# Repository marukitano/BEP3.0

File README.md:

# BEP3.0

**BEP3.0** is an electronics interface for classic BMW K-series motorcycles.

It was developed to make replacing the original instrument cluster ("Brotbox")
with an aftermarket speedometer easier while keeping the original wiring loom
as intact and reversible as possible.

This repository contains the **production and manufacturing files** for the
BEP3.0.

> **License notice:** The files in this repository may be copied, modified and
> used to build a BEP3.0 for **private, non-commercial purposes**.
> **Commercial use is prohibited.**
>
> The commercial right to sell BEP3.0 units is reserved exclusively to
> **Marcus Knop**. Third-party commercial manufacturing or sales require his
> explicit written permission.

## Supported motorcycles

The BEP3.0 was designed for the classic BMW K-series, including:

- BMW K75
- BMW K100
- BMW K1
- BMW K1100

Compatibility with a particular aftermarket instrument depends on the signals
and inputs supported by that instrument.

## What is in this repository?

The repository contains the files used to produce the BEP3.0 hardware, including
PCB/manufacturing data and related production files.

The files are published so that the project can be studied, preserved, repaired
and rebuilt by private users.

## License

### Allowed

- ✅ View and study the files
- ✅ Copy the files for private, non-commercial use
- ✅ Modify the files for private, non-commercial use
- ✅ Build your own BEP3.0 for private, non-commercial use
- ✅ Have a board manufactured for your own private, non-commercial use
- ✅ Share the files non-commercially if the license and attribution remain

### Not allowed

- ❌ Sell BEP3.0 units
- ❌ Sell bare PCBs based on the BEP3.0 design
- ❌ Sell kits based on the BEP3.0 design
- ❌ Offer paid manufacturing or assembly based on these files
- ❌ Use the BEP3.0 design, or substantial parts of it, in another commercial product
- ❌ Use the files for crowdfunding, pre-orders or other commercial fundraising

**All commercial rights remain reserved by Marcus Knop.**

Only Marcus Knop may offer BEP3.0 products for commercial sale. Commercial
manufacturing by third parties is only permitted with his explicit written
permission.

See [LICENSE](LICENSE) for the complete license terms.

> Because commercial use is restricted, this project is **source-available for
> private/non-commercial use** rather than open source in the OSI/open-hardware
> sense.

## Project page

More information about the BEP3.0:

https://maru-labs.com/portfolio/bep3-0-5/

## Contributions and issues

If you discover an error in the production files or documentation, please open
an issue before manufacturing a board.

## Disclaimer

The files are provided **as-is**, without warranty.

If you manufacture hardware from these files, you are responsible for checking
the design, component choices, manufacturing data, electrical safety and
suitability for your intended use.

---

**BEP3.0 / Maru Labs**  
Copyright © Marcus Knop

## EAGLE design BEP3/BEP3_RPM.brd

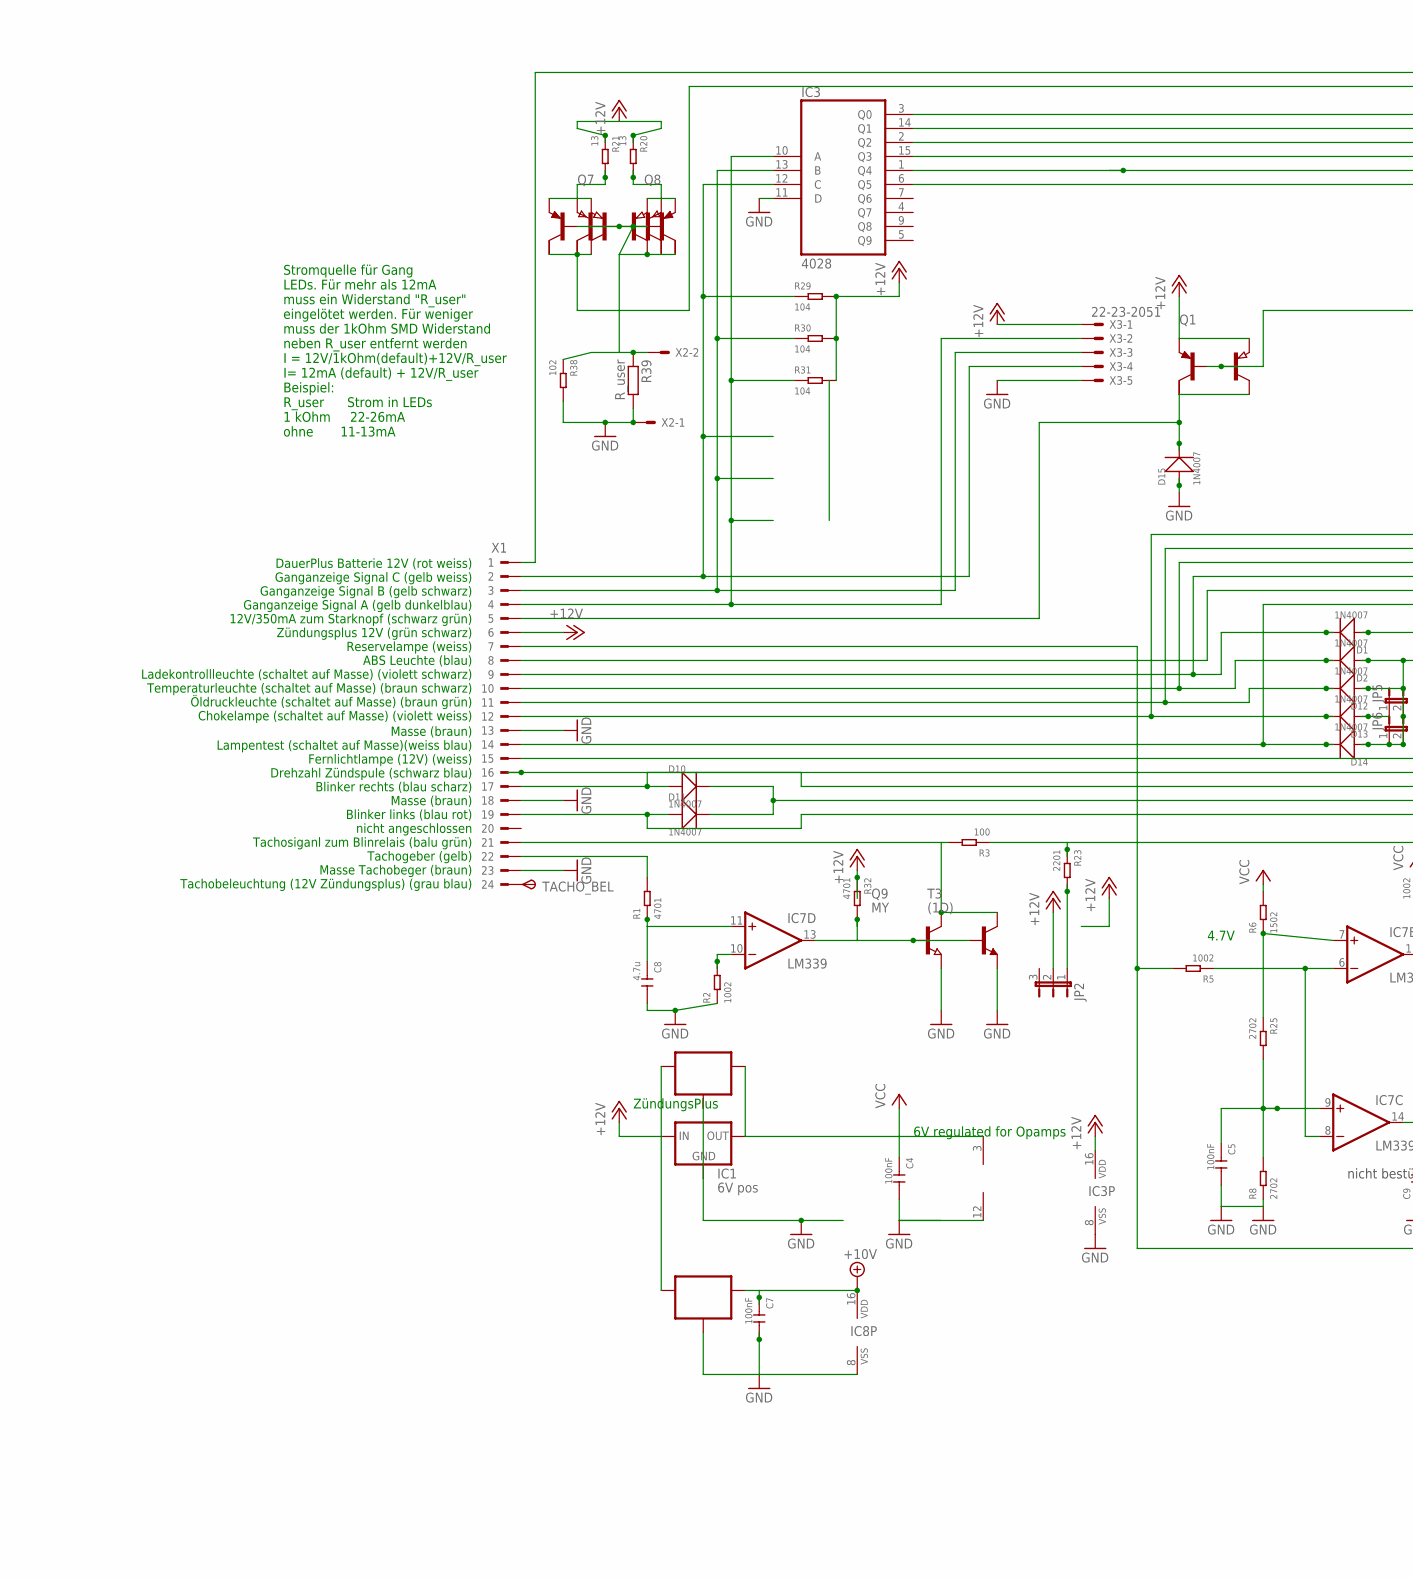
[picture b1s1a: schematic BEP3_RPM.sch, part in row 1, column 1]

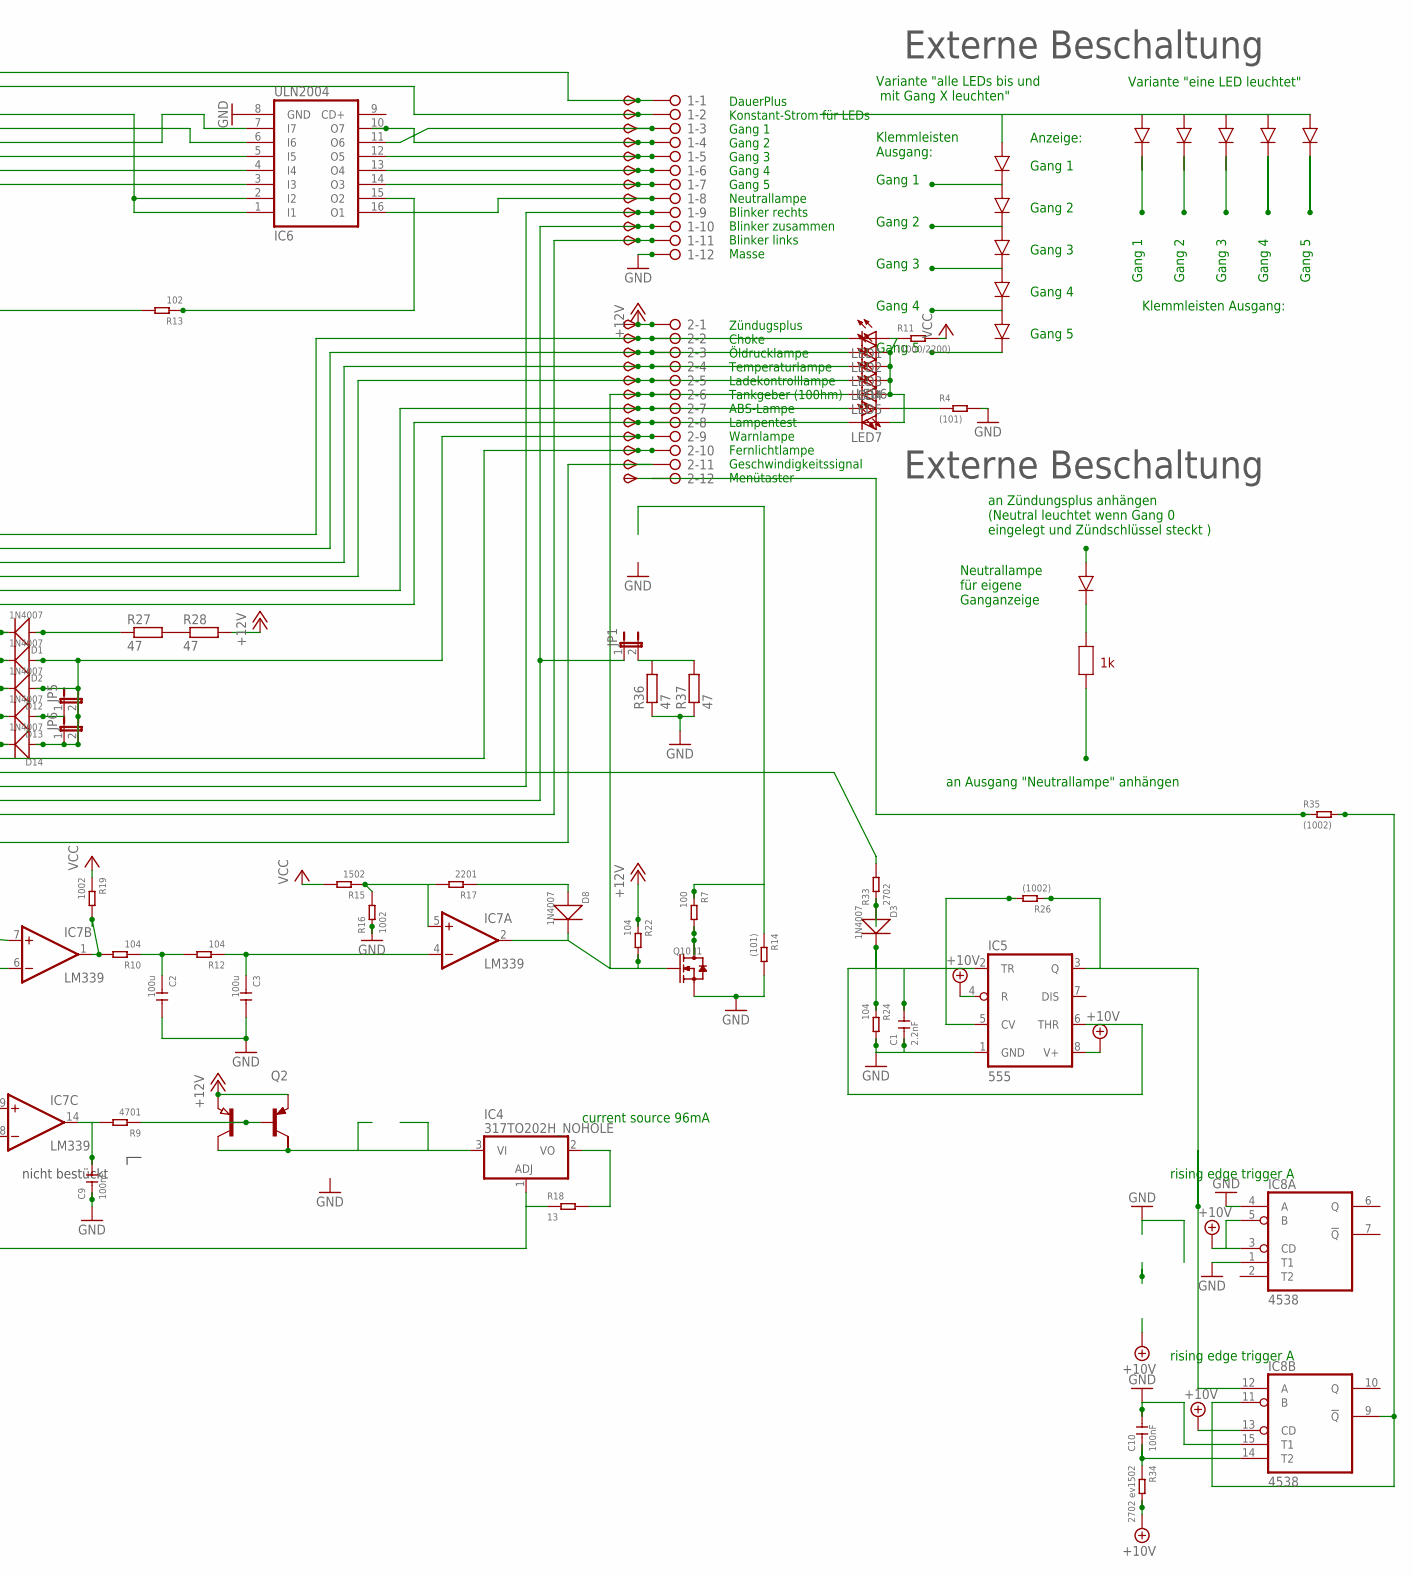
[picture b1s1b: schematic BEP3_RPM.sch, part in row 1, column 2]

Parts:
1, 2: 2081-1132; 12-PIN
C1: 2.2nF; C0805
C2, C3: 100u; C1206
C4, C5, C7, C9, C10: 100nF; C0805
C8: 4.7u; C0805
D1, D3, D10, D11, D15: 1N4007; DO-214AC
D2, D8, D12, D13, D14: 1N4007; DO-214AC-1206MOUNT
IC1: 6V pos; 78LXX
IC2, IC9: 78LXX-SOT89; SOT89
IC3: 4028; SO16
IC4: 317TO202H_NOHOLE; TO220H_NOHOLE
IC5: 555; SO08
IC6: ULN2004; SO16
IC7: LM339; SO14
IC8: 4538; SO16
JP1, JP5, JP6: JP1E; JP1
JP2: JP2E; JP2
LED1, LED2, LED3, LED4, LED5, LED6, LED7: LEDLD260; LD260
Q1, Q2, Q7, Q8: PNP-TRANSISTOR_SOT89; SOT89
Q3: AH-16; SOT223
Q4, Q5, Q6: (AH-16); SOT223
Q9: MY; SOT89
Q10: J1; SOT-23
R1, R9, R32: 4701; R0805
R2, R5, R16, R19: 1002; R0805
R3, R7: 100; R0805
R4, R14: (101); R0805
R6, R15: 1502; R0805
R8, R25, R33: 2702; R0805
R10, R12, R22, R24, R29, R30, R31: 104; R0805
R11: (1000/2200); R0805
R13, R38: 102; R0805
R17, R23: 2201; R0805
R18, R20, R21: 13; R1206
R26, R35: (1002); R0805
R27, R28, R36, R37: 47; V235/17_1MM
R34: 2702 ev1502; R0805
R39: R_user; R0805
T1: PNP2SM8; SM8
T3: (1D); SOT23-BEC
TACHO_BEL: TPSP1_1MM; P1_1.0MM
TP1, TP2, TP3, TP4, TP5, TP6, TP7, TP8, TP9, TP10, TP11, TP12, TP16, TP17, TP18, TP19, TP21, TP22, TP23, TP25, TP26: TPSB1.8; B1.8
TP13, TP24: TPSB1,27; B1,27
X1: CON_BMWV2; 24-PIN_V2
X2: 22-23-2021
X3: 22-23-2051

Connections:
+10V: C7.1, IC5.4 (R), IC5.8 (V+), IC8.3 (CD), IC8.5 (B), IC8.13 (CD), IC8.16 (VDD), IC9.1 (OUT), R34.2
+12V: 2.1, IC1.IN, IC2.3 (IN), IC3.16 (VDD), IC9.3 (IN), JP2.2, Q1.3 (E), Q2.3 (E), Q3.3 (E), Q4.3 (E), R20.1, R21.1, R22.1, R28.2, R29.2, R30.2, R31.2, R32.1, TP12.TP, X1.6, X3.1
GND: 1.12, C1.1, C2.2, C3.2, C4.2, C5.2, C7.2, C8.2, C9.1, C10.2, D15.1 (+), IC1.GND, IC2.2 (GND), IC2.4 (GND), IC3.8 (VSS), IC3.11 (D), IC5.1 (GND), IC6.8 (GND), IC7.12 (GND), IC8.1 (T1), IC8.4 (A), IC8.8 (VSS), IC8.15 (T1), Q9.3 (E), Q10.2 (S), R2.1, R4.2, R8.1, R14.2, R16.1, R24.2, R36.1, R37.1, R38.2, R39.2, T3.E, X1.13, X1.18, X1.23, X2.1, X3.5
unnamed: 2.9, D2.1 (+), D12.1 (+), D14.1 (+), JP5.2, JP6.1, JP6.2, TP24.TP
unnamed: IC3.10 (A), R31.1, X1.4, X3.2
unnamed: IC3.13 (B), R30.1, X1.3, X3.3
unnamed: 2.7, LED6.A, TP22.TP, X1.8
unnamed: Q5.3 (E), Q8.3 (E), R21.2, T1.1 (E)
unnamed: IC7.10 (-IN), R2.2
unnamed: R27.2, R28.1
unnamed: Q6.3 (E), Q7.3 (E), R20.2, T1.3 (E)
unnamed: D15.2 (-), Q1.2 (C), Q3.2 (C), X1.5
unnamed: 2.2, D13.2 (-), LED1.K (C), TP16.TP, X1.12
unnamed: 2.3, D12.2 (-), LED2.K (C), TP17.TP, X1.11
unnamed: 2.4, D2.2 (-), LED3.K (C), TP18.TP, X1.10
unnamed: IC4.3 (VI), Q2.2 (C), Q4.2 (C)
unnamed: IC7.6 (-IN), IC7.8 (-IN), R5.1
unnamed: IC3.12 (C), R29.1, X1.2, X3.4
unnamed: IC3.15 (Q3), IC6.5 (I5)
unnamed: 2.8, D14.2 (-), LED7.K (C), TP23.TP, X1.14
unnamed: 1.9, D10.1 (+), TP9.TP, X1.17
unnamed: 1.11, D11.1 (+), TP11.TP, X1.19
unnamed: IC8.9 (!Q), IC8.11 (B), R35.2
unnamed: R1.2, X1.22
unnamed: C8.1, IC7.11 (+IN), R1.1
unnamed: 1.6, IC6.13 (O4), TP6.TP
unnamed: 1.7, IC6.14 (O3), TP7.TP
unnamed: 2.11, R3.1, R23.1, TP26.TP
unnamed: R7.1, R14.1
unnamed: JP2.1, R23.2
unnamed: C5.1, IC7.9 (+IN), R8.2, R25.2
unnamed: C9.2, IC7.14 (OUT), R9.2
unnamed: C1.2, D3.2 (-), IC5.2 (TR), IC5.6 (THR), R24.1
unnamed: LED6.K (C), R4.1
unnamed: IC4.1 (ADJ), R5.2, R18.1, X1.7
unnamed: Q2.1 (B), Q4.1 (B), R9.1
unnamed: IC3.2 (Q2), IC6.7 (I7)
unnamed: 1.3, IC6.11 (O6), TP3.TP
unnamed: 1.5, IC6.12 (O5), TP5.TP
unnamed: LED1.A, LED2.A, LED3.A, LED4.A, LED5.A, LED7.A, R11.1
unnamed: R33.2, X1.16
unnamed: Q1.1 (B), Q3.1 (B), R13.2
unnamed: IC3.3 (Q0), IC6.1 (I1), IC6.2 (I2)
unnamed: C2.1, R10.1, R12.2
unnamed: C3.1, IC7.4 (-IN), R12.1
unnamed: IC7.5 (+IN), R15.1, R16.2, R17.2
unnamed: Q10.3 (D), R7.2
unnamed: D8.1 (+), R17.1
unnamed: IC3.1 (Q4), IC6.4 (I4)
unnamed: 1.8, IC6.16 (O1), TP8.TP
unnamed: 2.10, TP25.TP, X1.15
unnamed: D1.1 (+), R27.1
unnamed: 2.5, D1.2 (-), LED4.K (C), TP19.TP, X1.9
unnamed: IC3.14 (Q1), IC6.6 (I6)
unnamed: Q5.1 (B), Q6.1 (B), Q6.2 (C), Q7.1 (B), Q7.2 (C), Q8.1 (B), R38.1, R39.1, T1.2 (B), T1.4 (B), T1.6 (C1), X2.2
unnamed: TACHO_BEL.TP, X1.24
unnamed: 1.2, Q5.2 (C), Q8.2 (C), T1.8 (C1), TP2.TP
unnamed: 2.6, D8.2 (-), IC7.2 (OUT), LED5.K (C), Q10.1 (G), R22.2, TP21.TP
unnamed: IC3.6 (Q5), IC6.3 (I3)
unnamed: IC4.2 (VO), R18.2
unnamed: IC5.5 (CV), R26.2
unnamed: 1.4, IC6.10 (O7), TP4.TP
unnamed: 1.1, TP1.TP, X1.1
unnamed: IC7.7 (+IN), R6.1, R25.1
unnamed: Q9.2 (C), R3.2, T3.C, X1.21
unnamed: IC7.13 (OUT), Q9.1 (B), R32.2, T3.B
unnamed: IC5.3 (Q), IC8.12 (A), R26.1
unnamed: D3.1 (+), R33.1
unnamed: IC6.15 (O2), R13.1
unnamed: C10.1, IC8.14 (T2), R34.1
unnamed: 2.12, R35.1, TP13.TP
unnamed: 1.10, D10.2 (-), D11.2 (-), JP1.1, TP10.TP
unnamed: JP1.2, R36.2, R37.2
unnamed: D13.1 (+), JP5.1
unnamed: IC7.1 (OUT), R10.2, R19.2
VCC: C4.1, IC1.OUT, IC2.1 (OUT), IC7.3 (V+), R6.2, R11.2, R15.2, R19.1

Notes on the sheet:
6V regulated for Opamps
current source 96mA
ZündungsPlus
Zündugsplus Choke Öldrucklampe Temperaturlampe Ladekontrolllampe Tankgeber (100hm) ABS-Lampe Lampentest Warnlampe Fernlichtlampe Geschwindigkeitssignal Menütaster
DauerPlus Konstant-Strom für LEDs Gang 1 Gang 2 Gang 3 Gang 4 Gang 5 Neutrallampe Blinker rechts Blinker zusammen Blinker links Masse
DauerPlus Batterie 12V (rot weiss) Ganganzeige Signal C (gelb weiss) Ganganzeige Signal B (gelb schwarz) Ganganzeige Signal A (gelb dunkelblau) 12V/350mA zum Starknopf (schwarz grün) Zündungsplus 12V (grün schwarz) Reservelampe (weiss) ABS Leuchte (blau) Ladekontrollleuchte (schaltet auf Masse) (vi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
Masse (braun) Lampentest (schaltet auf Masse)(weiss blau) Fernlichtlampe (12V) (weiss) Drehzahl Zündspule (schwarz blau) Blinker rechts (blau scharz) Masse (braun) Blinker links (blau rot) nicht angeschlossen Tachosiganl zum Blinrelais (balu grün) Tachogeber (gelb) Masse Tachobeger (braun) Tachobel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
4.7V
Stromquelle für Gang LEDs. Für mehr als 12mA muss ein Widerstand "R_user" eingelötet werden. Für weniger muss der 1kOhm SMD Widerstand neben R_user entfernt werden I = 12V/1kOhm(default)+12V/R_user I= 12mA (default) + 12V/R_user Beispiel: R_user Strom in LEDs 1 kOhm 22-26mA ohne 11-13mA
Gang 1
Gang 2
Gang 3
Gang 4
Gang 5
Variante "eine LED leuchtet"
Variante "alle LEDs bis und mit Gang X leuchten"
Klemmleisten Ausgang:
Klemmleisten Ausgang:
an Zündungsplus anhängen (Neutral leuchtet wenn Gang 0 eingelegt und Zündschlüssel steckt )
an Ausgang "Neutrallampe" anhängen
Neutrallampe für eigene Ganganzeige
Externe Beschaltung
Anzeige:
nicht bestückt
rising edge trigger A

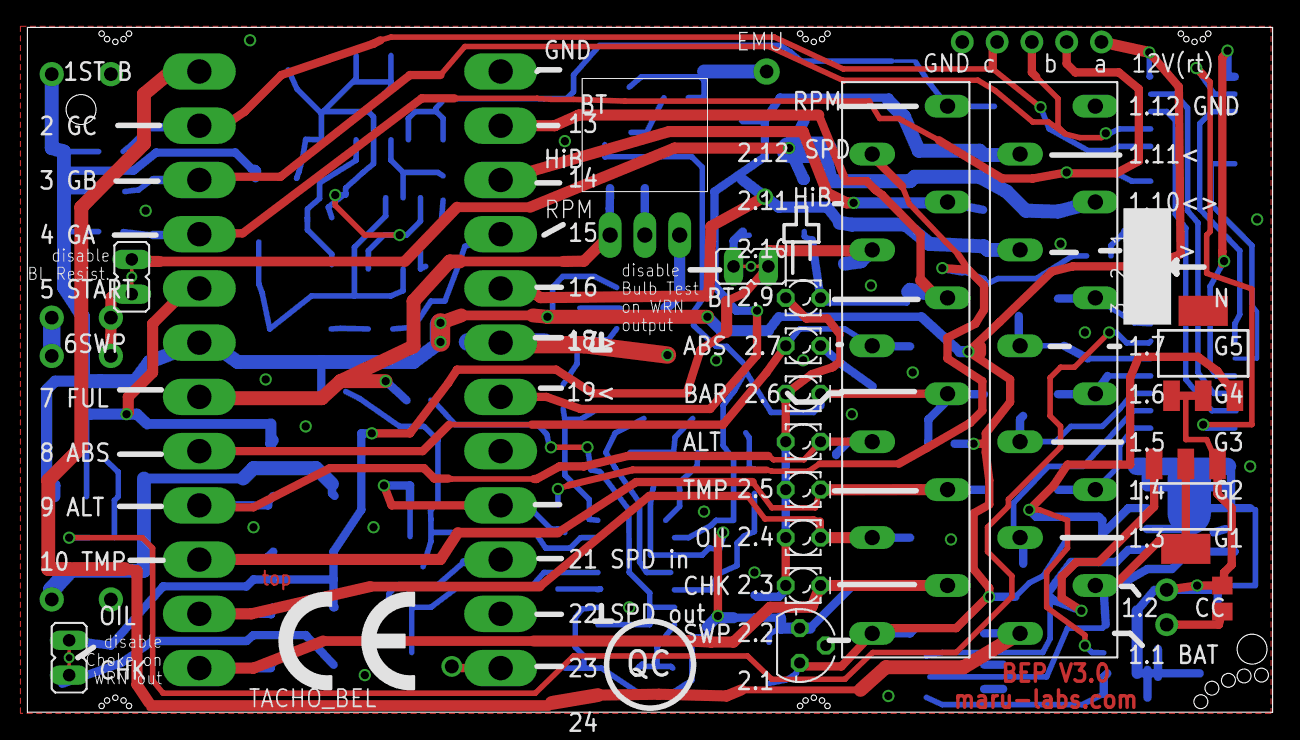
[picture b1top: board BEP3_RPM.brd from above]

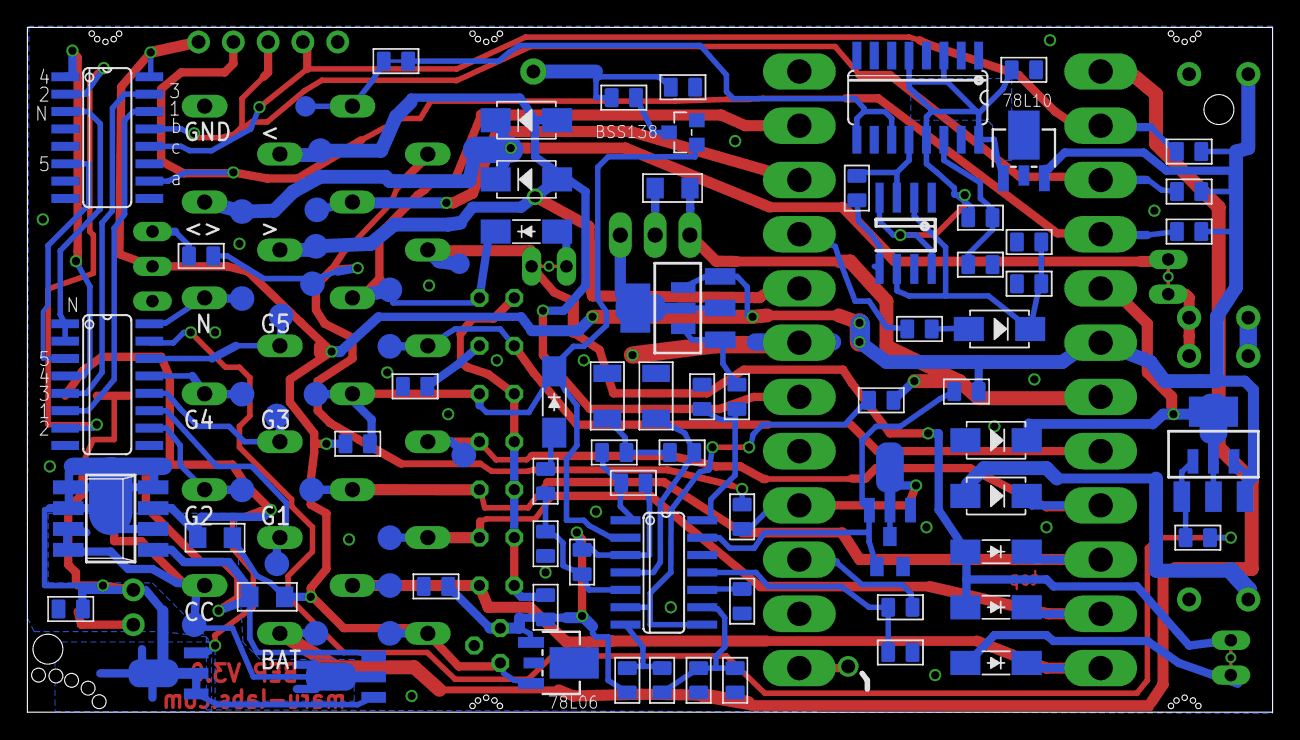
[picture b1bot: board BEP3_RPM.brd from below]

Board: 2 copper layers, 90.9 x 50.0 mm, 120 parts (94 on the bottom side), 76 nets.

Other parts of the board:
U$1: CE_10.00

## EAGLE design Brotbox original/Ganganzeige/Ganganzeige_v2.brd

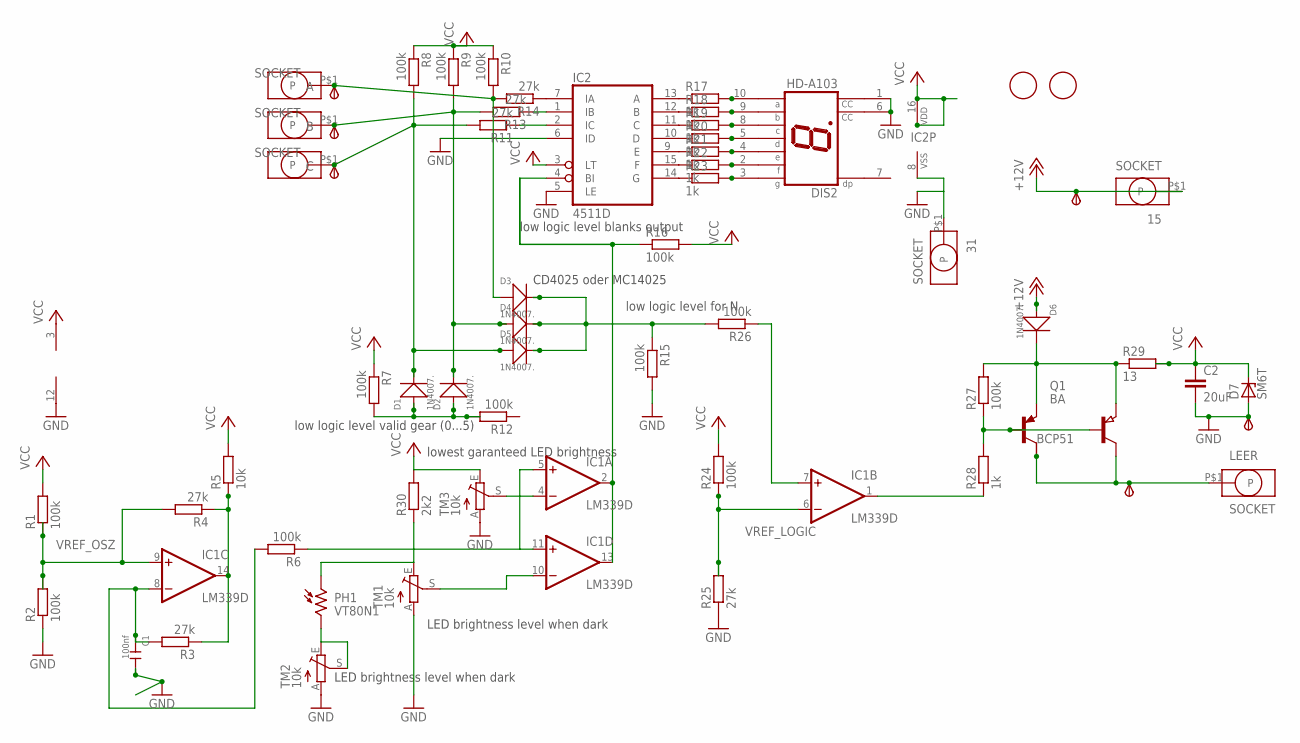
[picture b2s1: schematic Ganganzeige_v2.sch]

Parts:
15, 31: SOCKET; ID2.5MM
15_: TPSB2.0; B2.0
A: SOCKET; ID2.5MM
A_: TPSB2.0; B2.0
B: SOCKET; ID2.5MM
B_: TPSB2.0; B2.0
C: SOCKET; ID2.5MM
C1: 100nf; C0805
C2: 20uF; C1206K
C_: TPSB2.0; B2.0
D1, D2, D3, D4, D5, D6: 1N4007.; DO-214AC
D7: SM6T; DO214AA
DIS2: HD-A103; HDSP-A
FID1, FID2: FIDUCIAL; FIDUCIAL_1MM
GND_: TPSB2.0; B2.0
IC1: LM339D; SO14
IC2: 4511D; SO16
LEER: SOCKET; ID2.5MM
LEER_: TPSB2.0; B2.0
PH1: VT80N1; VT800
Q1: BA; SOT89
R1, R2, R6, R7, R8, R9, R10, R12, R15, R16, R24, R26, R27: 100k; R0805
R3, R4, R11, R13, R14, R25: 27k; R0805
R5: 10k; R0805
R17, R18, R19, R20, R21, R22, R23, R28: 1k; R0805
R29: 13; R1206
R30: 2k2; R0805
T: BCP53T1; SOT223
TM1, TM2, TM3: 10k; S63X

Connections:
+12V: 15.P$1, 15_.TP, D6.1 (+)
GND: 31.P$1, C1.2, C2.2, D7.A, DIS2.1 (CC), DIS2.6 (CC), GND_.TP, IC1.12 (GND), IC2.5 (LE), IC2.6 (ID), IC2.8 (VSS), R2.1, R15.2, R25.1, TM1.A, TM2.A, TM3.A
unnamed: IC2.13 (A), R17.1
unnamed: DIS2.10 (A), R17.2
unnamed: IC2.12 (B), R18.1
unnamed: DIS2.9 (B), R18.2
unnamed: IC2.11 (C), R19.1
unnamed: DIS2.8 (C), R19.2
unnamed: IC2.10 (D), R20.1
unnamed: DIS2.5 (D), R20.2
unnamed: IC2.9 (E), R21.1
unnamed: PH1.1, R30.1, TM1.E
unnamed: DIS2.4 (E), R21.2
unnamed: IC2.15 (F), R22.1
unnamed: DIS2.2 (F), R22.2
unnamed: IC2.14 (G), R23.1
unnamed: DIS2.3 (G), R23.2
unnamed: A.P$1, A_.TP, D3.1 (+), R10.2, R14.2
unnamed: B.P$1, B_.TP, D2.2 (-), D4.1 (+), R9.2, R13.2
unnamed: C.P$1, C_.TP, D1.2 (-), D5.1 (+), R8.2, R11.2
unnamed: IC1.1 (OUT), R28.1
unnamed: Q1.1 (B), R27.1, R28.2, T.1 (B)
unnamed: PH1.2, TM2.E, TM2.S
unnamed: C1.1, IC1.8 (-IN), R3.2, R6.2
unnamed: IC1.14 (OUT), R3.1, R4.1, R5.1
unnamed: D1.1 (+), D2.1 (+), R7.2, R12.2
unnamed: IC1.2 (OUT), IC1.13 (OUT), IC2.4 (BI), R16.1
unnamed: IC1.5 (+IN), IC1.11 (+IN), R6.1
unnamed: IC1.10 (-IN), TM1.S
unnamed: IC1.4 (-IN), TM3.S
unnamed: IC1.7 (+IN), R26.1
unnamed: IC2.7 (IA), R14.1
unnamed: D3.2 (-), D4.2 (-), D5.2 (-), R15.1, R26.2
unnamed: IC2.2 (IC), R11.1
unnamed: IC2.1 (IB), R13.1
VCC: C2.1, D7.C, IC1.3 (V+), IC2.3 (LT), IC2.16 (VDD), R1.2, R5.2, R7.1, R8.1, R9.1, R10.1, R16.2, R24.2, R29.2, R30.2, TM3.E
VREF_LOGIC: IC1.6 (-IN), R24.1, R25.2
VREF_OSZ: IC1.9 (+IN), R1.1, R2.2, R4.2
ZUENDPLUS_OUT: LEER.P$1, LEER_.TP, Q1.2 (C), T.2 (C)
ZUEND_EIN: D6.2 (-), Q1.3 (E), R27.2, R29.1, T.3 (E)

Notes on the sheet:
CD4025 oder MC14025
low logic level for N
low logic level valid gear (0...5)
low logic level blanks output
LED brightness level when dark
lowest garanteed LED brightness

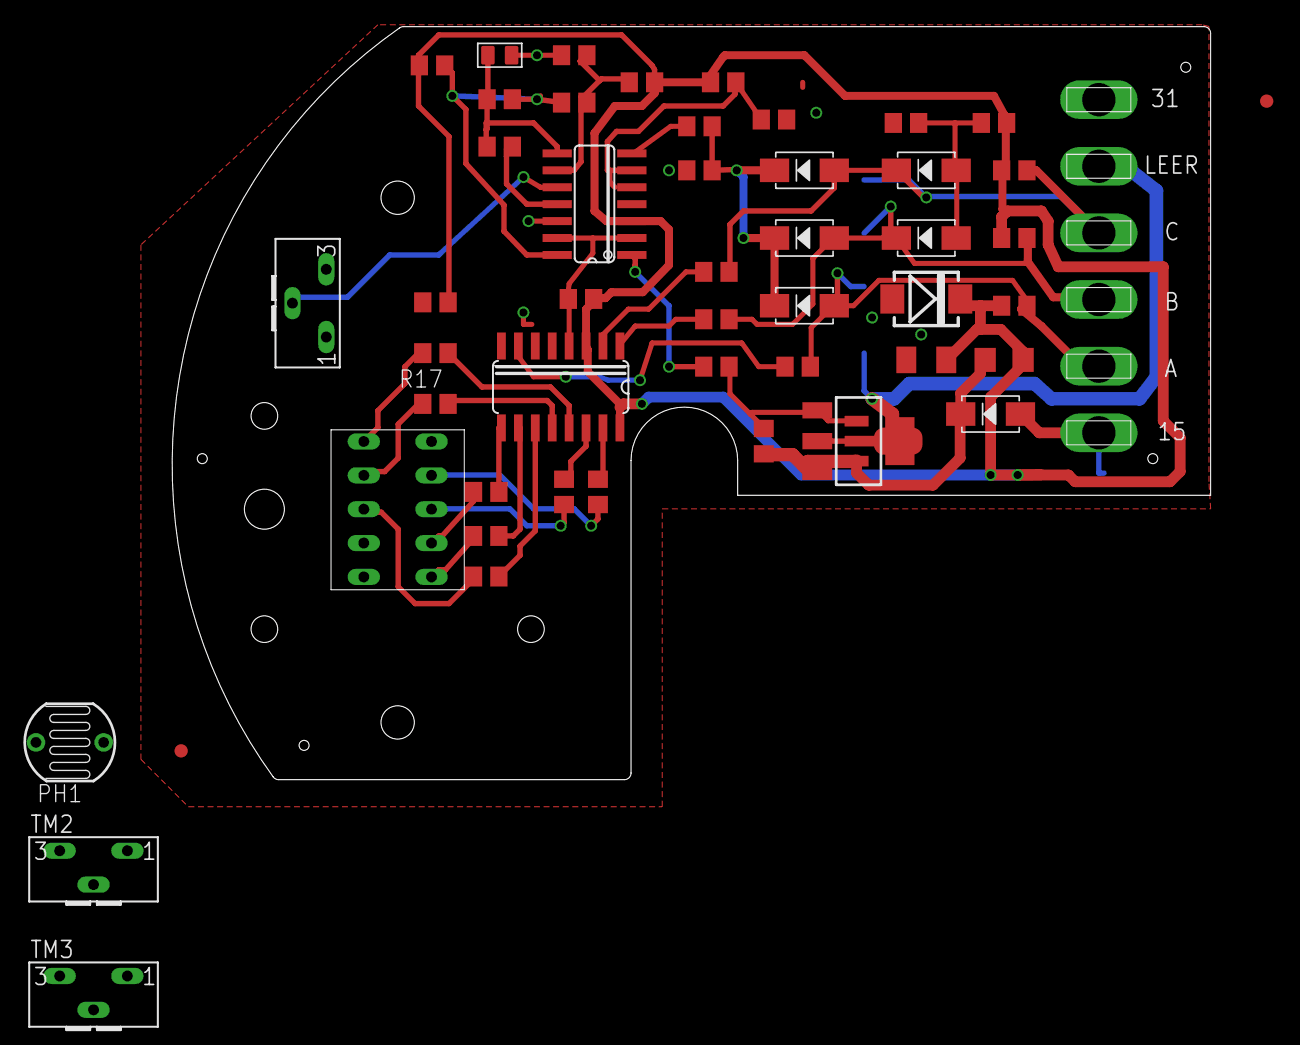
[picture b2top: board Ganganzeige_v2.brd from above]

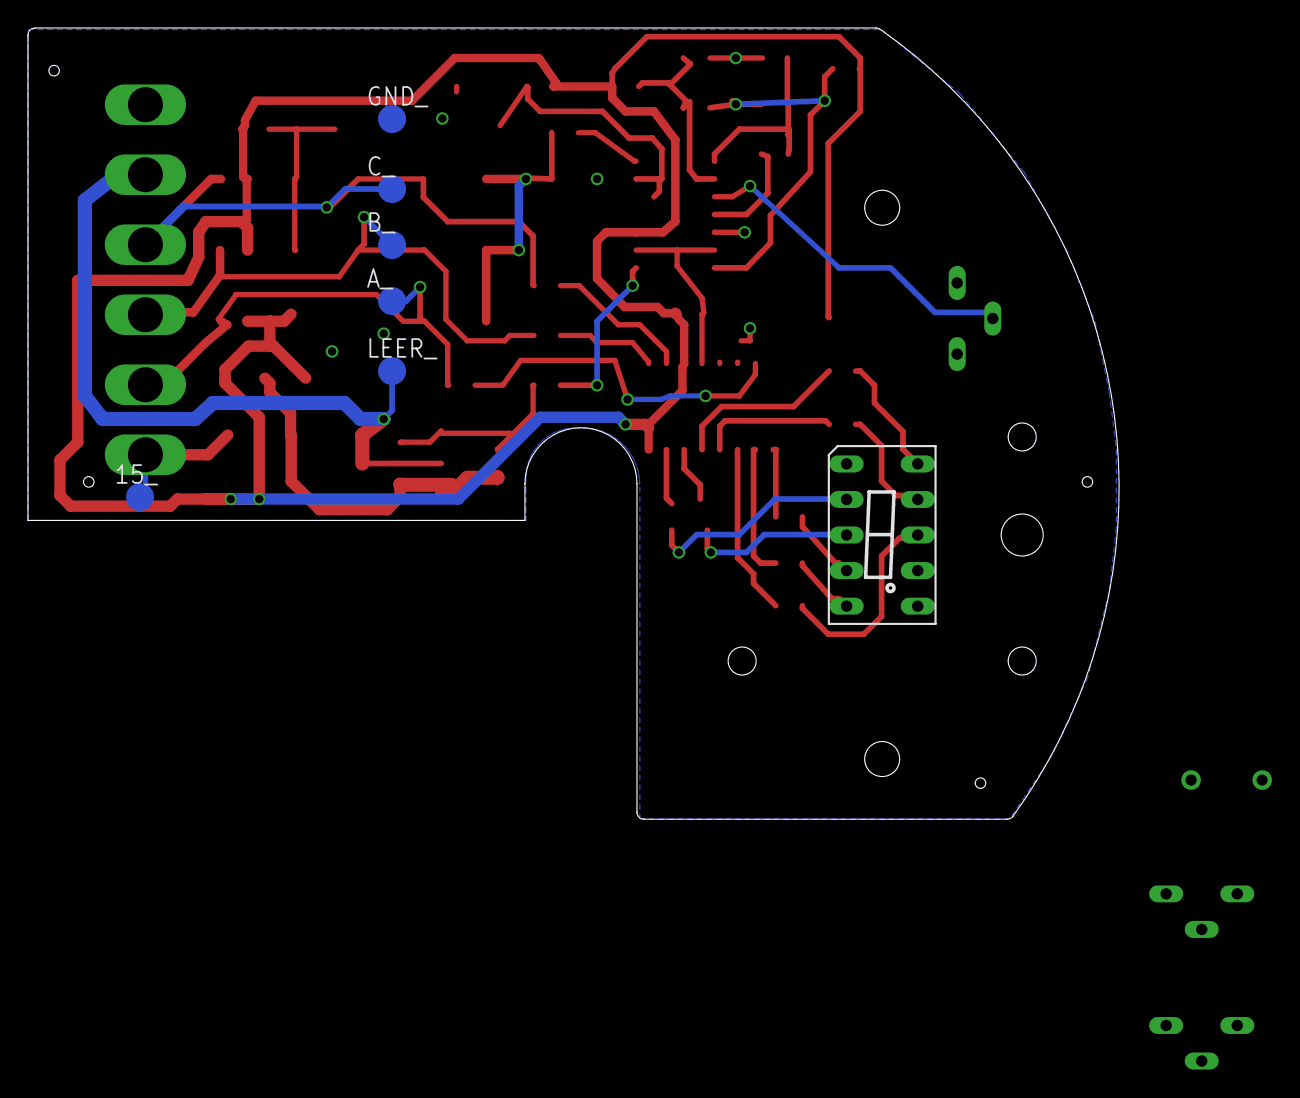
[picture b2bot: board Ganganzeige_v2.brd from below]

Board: 2 copper layers, 77.9 x 56.5 mm, 62 parts (7 on the bottom side), 40 nets.
